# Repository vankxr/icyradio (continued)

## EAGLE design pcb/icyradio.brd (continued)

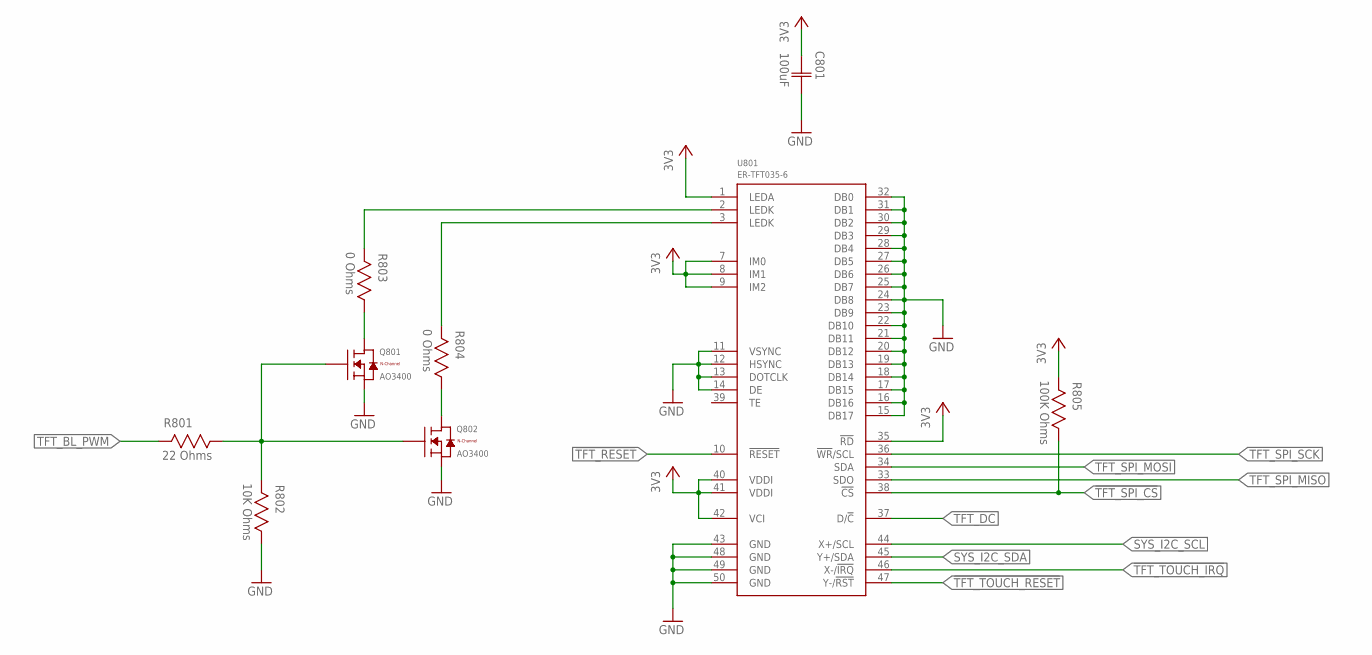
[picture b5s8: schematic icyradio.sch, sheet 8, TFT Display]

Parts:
C801: 100uF; CAP1206
Q801, Q802: AO3400; SOT23
R801: 22 Ohms; RES0603
R802: 10K Ohms; RES0603
R803, R804: 0 Ohms; RES0603
R805: 100K Ohms; RES0603
U801: ER-TFT035-6; FPC-50P

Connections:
3V3: C801.1 (C1), R805.2, U801.1 (LEDA), U801.7 (IM0), U801.8 (IM1), U801.9 (IM2), U801.35 (!RD), U801.40 (VDDI), U801.41 (VDDI), U801.42 (VCI); also elsewhere on the board
!TFT_RESET: U801.10 (!RESET); also elsewhere on the board
!TFT_SPI_CS: R805.1, U801.38 (!CS); also elsewhere on the board
!TFT_TOUCH_IRQ: U801.46 (X-/!IRQ!); also elsewhere on the board
!TFT_TOUCH_RESET: U801.47 (Y-/!RST!); also elsewhere on the board
GND: C801.2 (C2), Q801.2 (S), Q802.2 (S), R802.1, U801.11 (VSYNC), U801.12 (HSYNC), U801.13 (DOTCLK), U801.14 (DE), U801.15 (DB17), U801.16 (DB16), U801.17 (DB15), U801.18 (DB14), U801.19 (DB13), U801.20 (DB12), U801.21 (DB11), U801.22 (DB10), U801.23 (DB9), U801.24 (DB8), U801.25 (DB7), U801.26 (DB6), U801.27 (DB5), U801.28 (DB4), U801.29 (DB3), U801.30 (DB2), U801.31 (DB1), U801.32 (DB0), U801.43 (GND), U801.48 (GND), U801.49 (GND), U801.50 (GND); also elsewhere on the board
unnamed: Q802.3 (D), R804.1
unnamed: Q801.3 (D), R803.1
unnamed: Q801.1 (G), Q802.1 (G), R801.1, R802.2
SYS_I2C_SCL: U801.44 (X+/SCL); also elsewhere on the board
SYS_I2C_SDA: U801.45 (Y+/SDA); also elsewhere on the board
TFT_BL_K1: R803.2, U801.2 (LEDK)
TFT_BL_K2: R804.2, U801.3 (LEDK)
TFT_BL_PWM: R801.2; also elsewhere on the board
TFT_DC: U801.37 (D/!C!); also elsewhere on the board
TFT_SPI_MISO: U801.33 (SDO); also elsewhere on the board
TFT_SPI_MOSI: U801.34 (SDA); also elsewhere on the board
TFT_SPI_SCK: U801.36 (!WR!/SCL); also elsewhere on the board

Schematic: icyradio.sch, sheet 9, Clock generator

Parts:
C901, C902, C904, C905, C907: 100nF; CAP0603
C903, C906: DNP; CAP0603
R901, R902, R903: 100K Ohms; RES0603
R904, R905, R906, R907, R908, R909: 0 Ohms; RES0603
U901: DSC1201DE3-50M00000; VDFN6
U902: SI5351C; QFN20
X901: DNP; 4-SMD-3225

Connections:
3V3: C901.1 (C1), C902.1 (C1), C904.1 (C1), C905.1 (C1), C907.1 (C1), R902.2, R903.2, U901.6 (VDD), U902.10 (VDDOB), U902.11 (VDDOA), U902.14 (VDDOD), U902.18 (VDDOC), U902.20 (VDD); also elsewhere on the board
!CLK_MNGR_IRQ: R903.1, U902.3 (INTR); also elsewhere on the board
!CLK_MNGR_OE: R902.1, U902.7 (!OE); also elsewhere on the board
!CLK_MNGR_REFCLK_STDBY: R901.2, U901.1 (!STDBY); also elsewhere on the board
CLK_MNGR_CLK0: R904.2, U902.13 (CLK0)
CLK_MNGR_CLK1: R907.2, U902.12 (CLK1)
CLK_MNGR_CLK2: R905.2, U902.9 (CLK2)
CLK_MNGR_CLK3: R908.2, U902.8 (CLK3)
CLK_MNGR_CLK5: R909.2, U902.17 (CLK5)
CLK_MNGR_CLK6: R906.2, U902.16 (CLK6)
CLK_MNGR_REF: U901.4 (CLK), U902.6 (CLKIN)
CLK_MNGR_XTALA: C903.1 (C1), U902.1 (XA), X901.2 (1)
CLK_MNGR_XTALB: C906.1 (C1), U902.2 (XB), X901.4 (2)
DSP_MAIN_CLK: R906.1; also elsewhere on the board
FPGA_CLK1: R905.1; also elsewhere on the board
FPGA_CLK2: R907.1; also elsewhere on the board
FPGA_CLK3: R904.1; also elsewhere on the board
FPGA_CLK4: R908.1; also elsewhere on the board
GND: C901.2 (C2), C902.2 (C2), C903.2 (C2), C904.2 (C2), C905.2 (C2), C906.2 (C2), C907.2 (C2), R901.1, U901.3 (GND), U902.21 (GND), X901.1 (GND), X901.3 (GND); also elsewhere on the board
SMC_MAIN_CLK: R909.1; also elsewhere on the board
SYS_I2C_SCL: U902.4 (SCL); also elsewhere on the board
SYS_I2C_SDA: U902.5 (SDA); also elsewhere on the board

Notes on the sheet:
FPGA_CLK1 = 49.152 MHz (for 48 kHz audio sample rate) FPGA_CLK1 = 45.1584 MHz (for 44.1 kHz audio sample rate) FPGA_CLK2 = TBD MHz (general purpose clock) FPGA_CLK3 = TBD MHz (general purpose clock) FPGA_CLK4 = TBD MHz (general purpose clock) SMC_MAIN_CLK = 50 MHz (SMC main clock) DSP_MAIN_CLK = 20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

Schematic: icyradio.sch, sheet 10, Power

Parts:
C1001, C1002, C1006, C1010, C1011, C1015, C1017, C1020: 100nF; CAP0603
C1003, C1004, C1018, C1022, C1023, C1029, C1030: 4.7uF; CAP0603
C1005, C1008, C1012: 470pF; CAP0603
C1007, C1013, C1014, C1016: 100uF; CAP1206
C1009, C1019: 10nF; CAP0603
C1021, C1024, C1025, C1027, C1028: 1uF; CAP0603
C1026: 10uF; CAP0603
D1001: SP0503BAHT; SOT143
D1002, D1003: LED0603; 0603
F1001: PTC1206; 1206
L1001: 2.2uH; IND0805
L1002, L1004: 2.2uH; IND2520
L1003: 350nH; IND0805
L1005: 350nH; IND0603
R1001, R1002: 5.1K Ohms; RES0603
R1003: 274K Ohms; RES0603
R1004: 294K Ohms; RES0603
R1005, R1006, R1009, R1014, R1016: 100K Ohms; RES0603
R1007, R1010: 309K Ohms; RES0603
R1008: 64.9K Ohms; RES0603
R1011: 71.5K Ohms; RES0603
R1012: 510 Ohms; RES0603
R1013: 330 Ohms; RES0603
R1015: 820 Ohms; RES0603
U1001: MIC23155; DFN10
U1002: MIC23159; VQFN20
U1003: MIC2019; SOT23-6
U1004: ADP150UJZ-1.8; SOT23-5
U1005: ADP150UJZ-3.3; SOT23-5
U1006, U1007: MIC94305; DFN6
USB1001: USB-C-16P-SMD-FLAT-SIDE-TYPE-2

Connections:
1V2: C1006.1 (C1), C1007.1 (C1), L1001.1, R1003.2, U1002.17 (SNS); also elsewhere on the board
1V2_FB: R1003.1, R1004.2, U1002.16 (FB)
1V2_PGOOD: R1005.1, U1002.15 (PG); also elsewhere on the board
1V2_SOFTSTART: C1008.1 (C1), U1002.14 (SS)
1V8_CODEC_CLEAN: C1027.1 (C1), U1004.5 (OUT); also elsewhere on the board
3V3: C1015.1 (C1), C1016.1 (C1), C1024.1 (C1), L1004.2, R1005.2, R1006.2, R1009.2, R1010.2, R1013.2, R1016.2, U1002.10 (SNS), U1004.1 (VIN), U1004.3 (EN); also elsewhere on the board
3V3_ANA_RX_CLEAN: C1030.1 (C1), U1007.1 (VOUT), U1007.2 (VOUT); also elsewhere on the board
3V3_ANA_TXPLL_CLEAN: C1028.1 (C1), U1005.5 (OUT); also elsewhere on the board
3V3_ANA_TX_CLEAN: C1029.1 (C1), U1006.1 (VOUT), U1006.2 (VOUT); also elsewhere on the board
3V3_FB: R1010.1, R1011.2, U1002.11 (FB)
3V3_PGOOD: R1009.1, U1002.12 (PG); also elsewhere on the board
3V3_SOFTSTART: C1012.1 (C1), U1002.13 (SS)
3V6_ANA: C1010.1 (C1), C1013.1 (C1), C1022.1 (C1), C1023.1 (C1), C1025.1 (C1), L1002.2, R1007.2, U1001.3 (SNS), U1005.1 (VIN), U1005.3 (EN), U1006.4 (EN), U1006.5 (VIN), U1006.6 (VIN), U1007.4 (EN), U1007.5 (VIN), U1007.6 (VIN)
3V6_ANA_FB: R1007.1, R1008.2, U1001.4 (FB)
3V6_ANA_PGOOD: R1006.1, U1001.5 (PG); also elsewhere on the board
3V6_ANA_SOFTSTART: C1005.1 (C1), U1001.6 (SS)
5V0: C1001.1 (C1), C1002.1 (C1), C1003.1 (C1), C1004.1 (C1), C1011.1 (C1), C1014.1 (C1), C1017.1 (C1), C1018.1 (C1), C1019.1 (C1), L1003.2, L1005.1, R1012.2, U1001.2 (EN), U1001.8 (VIN), U1001.9 (VIN), U1002.1 (VIN), U1002.6 (VIN), U1002.7 (AVIN), U1002.9 (EN), U1002.18 (EN), U1002.20 (AVIN)
5V0_ANA_TXMIXER_CLEAN: C1020.1 (C1), C1021.1 (C1), L1005.2, U1003.1 (VIN); also elsewhere on the board
5V0_ANA_TXPA_CLEAN: C1026.1 (C1), U1003.6 (VOUT); also elsewhere on the board
!TXPA_OC: R1016.1, U1003.4 (!FAULT); also elsewhere on the board
DSP_D+: D1001.4, USB1001.A6 (D+), USB1001.B6 (D+); also elsewhere on the board
DSP_D-: D1001.3, USB1001.A7 (D-), USB1001.B7 (D-); also elsewhere on the board
GND: C1001.2 (C2), C1002.2 (C2), C1003.2 (C2), C1004.2 (C2), C1005.2 (C2), C1006.2 (C2), C1007.2 (C2), C1008.2 (C2), C1009.2 (C2), C1010.2 (C2), C1011.2 (C2), C1012.2 (C2), C1013.2 (C2), C1014.2 (C2), C1015.2 (C2), C1016.2 (C2), C1017.2 (C2), C1018.2 (C2), C1019.2 (C2), C1020.2 (C2), C1021.2 (C2), C1022.2 (C2), C1023.2 (C2), C1024.2 (C2), C1025.2 (C2), C1026.2 (C2), C1027.2 (C2), C1028.2 (C2), C1029.2 (C2), C1030.2 (C2), D1001.1, D1002.1 (C), D1003.1 (C), R1001.1, R1002.1, R1004.1, R1008.1, R1011.1, R1014.1, R1015.1, U1001.7 (AGND), U1001.10 (PGND), U1001.11 (PGND), U1002.2 (PGND), U1002.5 (PGND), U1002.8 (AGND), U1002.19 (AGND), U1002.21 (PGND), U1003.2 (GND), U1004.2 (GND), U1005.2 (GND), U1006.3 (GND), U1006.7 (GND), U1007.3 (GND), U1007.7 (GND), USB1001.A1/B12 (GND), USB1001.B1/A12 (GND); also elsewhere on the board
unnamed: L1004.1, U1002.4 (SW)
unnamed: L1001.2, U1002.3 (SW)
unnamed: R1001.2, USB1001.B5 (CC2)
unnamed: R1002.2, USB1001.A5 (CC1)
unnamed: F1001.2, USB1001.A4/B9 (VBUS), USB1001.B4/A9 (VBUS)
unnamed: L1002.1, U1001.1 (SW)
unnamed: C1009.1 (C1), D1001.2, F1001.1, L1003.1
unnamed: R1015.2, U1003.5 (ILIMIT)
unnamed: D1003.2 (A), R1013.1
unnamed: D1002.2 (A), R1012.1
TXPA_BIAS_EN: R1014.2, U1003.3 (EN); also elsewhere on the board

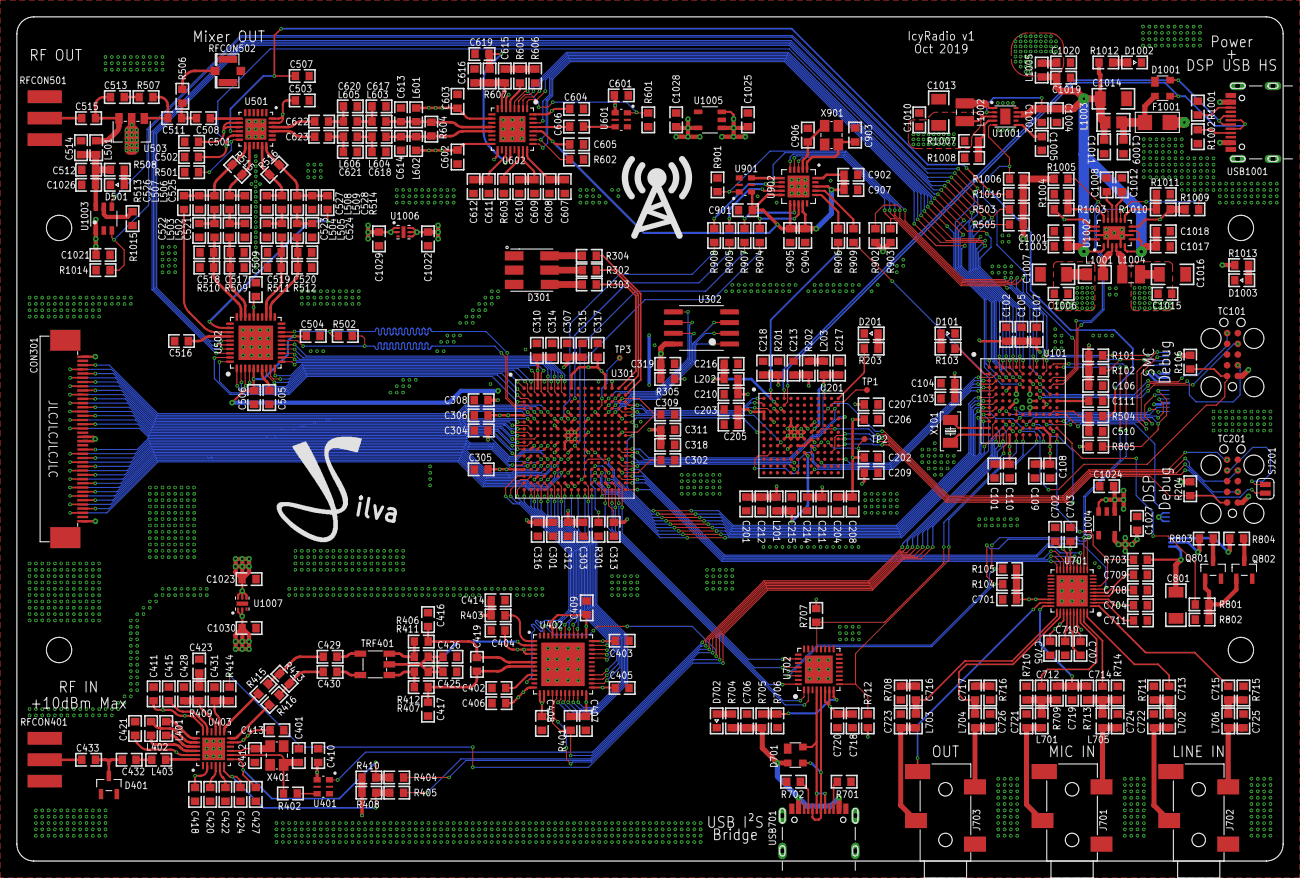
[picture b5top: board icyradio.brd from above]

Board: 4 copper layers, 150.0 x 100.0 mm, 386 parts (1 on the bottom side), 340 nets.

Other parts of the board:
U$1: JS_10MM
U$2: RADIO_10MM

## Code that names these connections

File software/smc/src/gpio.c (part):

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    // Port A
    GPIO->P[0].CTRL   = GPIO_P_CTRL_DRIVESTRENGTHALT_STRONG | (5 << _GPIO_P_CTRL_SLEWRATEALT_SHIFT)
                      | GPIO_P_CTRL_DRIVESTRENGTH_STRONG | (5 << _GPIO_P_CTRL_SLEWRATE_SHIFT);
    GPIO->P[0].MODEL  = GPIO_P_MODEL_MODE0_PUSHPULL                 // DSP_SPI_MOSI - USART3 - Location 0
                      | GPIO_P_MODEL_MODE1_INPUTPULL                // DSP_SPI_MISO - USART3 - Location 0
                      | GPIO_P_MODEL_MODE2_PUSHPULL                 // DSP_SPI_SCK - USART3 - Location 0
                      | GPIO_P_MODEL_MODE3_PUSHPULL                 // DSP_SPI_CS - USART3 - Location 0
                      | GPIO_P_MODEL_MODE4_DISABLED                 // NR
                      | GPIO_P_MODEL_MODE5_PUSHPULL                 // FPGA_SRESET
                      | GPIO_P_MODEL_MODE6_DISABLED                 // NR
                      | GPIO_P_MODEL_MODE7_PUSHPULL;                // TFT_SPI_MOSI - USART2 - Location 2
    GPIO->P[0].MODEH  = GPIO_P_MODEH_MODE8_INPUTPULL                // TFT_SPI_MISO - USART2 - Location 2
                      | GPIO_P_MODEH_MODE9_PUSHPULL                 // TFT_SPI_SCK - USART2 - Location 2
                      | GPIO_P_MODEH_MODE10_PUSHPULL                // TFT_SPI_CS - USART2 - Location 2
                      | GPIO_P_MODEH_MODE11_DISABLED                // NR
                      | GPIO_P_MODEH_MODE12_PUSHPULL                // RXADC_SHDN
                      | GPIO_P_MODEH_MODE13_PUSHPULL                // RXADC_DITH
                      | GPIO_P_MODEH_MODE14_PUSHPULL                // RXADC_GAIN
                      | GPIO_P_MODEH_MODE15_PUSHPULL;               // SMC_LED - TIM3 Channel 2 - Location 0
    GPIO->P[0].DOUT   = BIT(3) | BIT(5) | BIT(10) | BIT(12);
    GPIO->P[0].OVTDIS = 0;

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    GPIO->P[1].CTRL   = GPIO_P_CTRL_DRIVESTRENGTHALT_STRONG | (5 << _GPIO_P_CTRL_SLEWRATEALT_SHIFT)
                      | GPIO_P_CTRL_DRIVESTRENGTH_STRONG | (5 << _GPIO_P_CTRL_SLEWRATE_SHIFT);
    GPIO->P[1].MODEL  = GPIO_P_MODEL_MODE0_DISABLED                 // NR
                      | GPIO_P_MODEL_MODE1_INPUTPULLFILTER          // FPGA_CDONE
                      | GPIO_P_MODEL_MODE2_INPUTPULLFILTER          // FPGA_SMC_IRQ
                      | GPIO_P_MODEL_MODE3_DISABLED                 // NR
                      | GPIO_P_MODEL_MODE4_DISABLED                 // NR
                      | GPIO_P_MODEL_MODE5_INPUTPULLFILTER          // FPGA_CBSEL1
                      | GPIO_P_MODEL_MODE6_PUSHPULL                 // FPGA_CRESET
                      | GPIO_P_MODEL_MODE7_DISABLED;                // SMC_LFXTAL_P
    GPIO->P[1].MODEH  = GPIO_P_MODEH_MODE8_DISABLED                 // SMC_LFXTAL_N
                      | GPIO_P_MODEH_MODE9_DISABLED                 // NR
                      | GPIO_P_MODEH_MODE10_WIREDANDPULLUPFILTER    // DSP_RESET
                      | GPIO_P_MODEH_MODE11_DISABLED                // RXTUNER_IF_VAGC
                      | GPIO_P_MODEH_MODE12_PUSHPULL                // I2S_BRG_CFG
                      | GPIO_P_MODEH_MODE13_PUSHPULL                // I2S_BRG_RST
                      | GPIO_P_MODEH_MODE14_DISABLED                // SMC_MAIN_CLK
                      | GPIO_P_MODEH_MODE15_DISABLED;               // NR
    GPIO->P[1].DOUT   = BIT(1) | BIT(2) | BIT(5) | BIT(12);
    GPIO->P[1].OVTDIS = BIT(11);
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    // Port C
    GPIO->P[2].CTRL   = GPIO_P_CTRL_DRIVESTRENGTHALT_STRONG | (5 << _GPIO_P_CTRL_SLEWRATEALT_SHIFT)
                      | GPIO_P_CTRL_DRIVESTRENGTH_STRONG | (5 << _GPIO_P_CTRL_SLEWRATE_SHIFT);
    GPIO->P[2].MODEL  = GPIO_P_MODEL_MODE0_PUSHPULL                 // FPGA_SPI_CS - USART1 - Location 4
                      | GPIO_P_MODEL_MODE1_PUSHPULL                 // FPGA_SPI_SDI - USART1 - Location 4
                      | GPIO_P_MODEL_MODE2_INPUTPULL                // FPGA_SPI_SDO - USART1 - Location 4
                      | GPIO_P_MODEL_MODE3_PUSHPULL                 // FPGA_SPI_SCK - USART1 - Location 4
                      | GPIO_P_MODEL_MODE4_WIREDANDPULLUPFILTER     // RXTUNER_I2C_SDA - I2C1 - Location 0
                      | GPIO_P_MODEL_MODE5_WIREDANDPULLUPFILTER     // RXTUNER_I2C_SCL - I2C1 - Location 0
                      | GPIO_P_MODEL_MODE6_DISABLED                 // NR
                      | GPIO_P_MODEL_MODE7_DISABLED;                // NR
    GPIO->P[2].MODEH  = GPIO_P_MODEH_MODE8_INPUTPULLFILTER          // 3V3_PGOOD
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    // Port D
    GPIO->P[3].CTRL   = GPIO_P_CTRL_DRIVESTRENGTHALT_STRONG | (5 << _GPIO_P_CTRL_SLEWRATEALT_SHIFT)
                      | GPIO_P_CTRL_DRIVESTRENGTH_STRONG | (5 << _GPIO_P_CTRL_SLEWRATE_SHIFT);
    GPIO->P[3].MODEL  = GPIO_P_MODEL_MODE0_PUSHPULL                 // CODEC_RST
                      | GPIO_P_MODEL_MODE1_PUSHPULL                 // TFT_BL_PWM - TIM0 Channel 0 - Location 2
                      | GPIO_P_MODEL_MODE2_INPUTPULLFILTER          // TFT_TOUCH_IRQ
                      | GPIO_P_MODEL_MODE3_PUSHPULL                 // TFT_TOUCH_RESET
                      | GPIO_P_MODEL_MODE4_PUSHPULL                 // TFT_DC
                      | GPIO_P_MODEL_MODE5_DISABLED                 // NR
                      | GPIO_P_MODEL_MODE6_DISABLED                 // TXMIXER_TEMP
                      | GPIO_P_MODEL_MODE7_PUSHPULL;                // TFT_RESET
    GPIO->P[3].MODEH  = GPIO_P_MODEH_MODE8_DISABLED                 // NR
                      | GPIO_P_MODEH_MODE9_PUSHPULL                 // TXPLL_SDATA - USART4 - Location 1
                      | GPIO_P_MODEH_MODE10_DISABLED                // TXPLL_MUXOUT
                      | GPIO_P_MODEH_MODE11_PUSHPULL                // TXPLL_SCLK - USART4 - Location 1
                      | GPIO_P_MODEH_MODE12_PUSHPULL                // TXPLL_LE - USART4 - Location 1
                      | GPIO_P_MODEH_MODE13_PUSHPULL                // TXDAC_SCLK - USART5 - Location 1
                      | GPIO_P_MODEH_MODE14_DISABLED                // NR
                      | GPIO_P_MODEH_MODE15_DISABLED;               // RXTUNER_REFCLK_SEL - NU
    GPIO->P[3].DOUT   = BIT(2) | BIT(12);
    GPIO->P[3].OVTDIS = BIT(6) | BIT(10);

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                      | GPIO_P_MODEL_MODE1_DISABLED                 // NR
                      | GPIO_P_MODEL_MODE2_DISABLED                 // NR
                      | GPIO_P_MODEL_MODE3_DISABLED                 // NR
                      | GPIO_P_MODEL_MODE4_WIREDANDPULLUPFILTER     // SYS_I2C_SDA - I2C0 - Location 7
                      | GPIO_P_MODEL_MODE5_WIREDANDPULLUPFILTER     // SYS_I2C_SCL - I2C0 - Location 7
                      | GPIO_P_MODEL_MODE6_INPUTPULLFILTER          // CLK_MNGR_IRQ
                      | GPIO_P_MODEL_MODE7_DISABLED;                // NR
    GPIO->P[4].MODEH  = GPIO_P_MODEH_MODE8_PUSHPULL                 // TXDAC_SDIO - USART5 - Location 0
                      | GPIO_P_MODEH_MODE9_PUSHPULL                 // TXDAC_CS
                      | GPIO_P_MODEH_MODE10_PUSHPULL                // TXPA_BIAS_EN
                      | GPIO_P_MODEH_MODE11_INPUTPULLFILTER         // TXPA_OC
                      | GPIO_P_MODEH_MODE12_PUSHPULL                // TXDAC_RESET
                      | GPIO_P_MODEH_MODE13_INPUTPULLFILTER         // DSP_IRQ
                      | GPIO_P_MODEH_MODE14_DISABLED                // NR
                      | GPIO_P_MODEH_MODE15_PUSHPULL;               // TXMIXER_EN
    GPIO->P[4].DOUT   = BIT(6) | BIT(9) | BIT(11) | BIT(12) | BIT(13);
    GPIO->P[4].OVTDIS = 0;

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                      | GPIO_P_MODEL_MODE3_DISABLED                 // NC
                      | GPIO_P_MODEL_MODE4_DISABLED                 // NC
                      | GPIO_P_MODEL_MODE5_DISABLED                 // NR
                      | GPIO_P_MODEL_MODE6_PUSHPULL                 // CLK_MNGR_REFCLK_STDBY
                      | GPIO_P_MODEL_MODE7_PUSHPULL;                // TXPLL_EN
    GPIO->P[5].MODEH  = GPIO_P_MODEH_MODE8_PUSHPULL                 // TXPLL_MUTE
                      | GPIO_P_MODEH_MODE9_INPUTPULLFILTER          // TXPLL_LOCK
                      | GPIO_P_MODEH_MODE10_WIREDANDPULLUPFILTER    // AUDIO_I2C_SDA - I2C2 - Location 2
                      | GPIO_P_MODEH_MODE11_WIREDANDPULLUPFILTER    // AUDIO_I2C_SCL - I2C2 - Location 2
                      | GPIO_P_MODEH_MODE12_PUSHPULL                // CLK_MNGR_OE
                      | GPIO_P_MODEH_MODE13_DISABLED                // NC
                      | GPIO_P_MODEH_MODE14_DISABLED                // NC
                      | GPIO_P_MODEH_MODE15_DISABLED;               // NC
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
    // Debugger Route
    GPIO->ROUTEPEN &= ~(GPIO_ROUTEPEN_TDIPEN | GPIO_ROUTEPEN_TDOPEN);   // Disable JTAG
    GPIO->ROUTEPEN |= GPIO_ROUTEPEN_SWVPEN;                             // Enable SWO
    GPIO->ROUTELOC0 = GPIO_ROUTELOC0_SWVLOC_LOC0;                       // SWO on PF2

    // External interrupts
    GPIO->EXTIPSELL = GPIO_EXTIPSELL_EXTIPSEL0_PORTB            // FPGA_CDONE
                    | GPIO_EXTIPSELL_EXTIPSEL1_PORTB            // FPGA_SMC_IRQ
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
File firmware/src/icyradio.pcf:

set_io CLK1             C8      # IN    # Clock input 1
#set_io CLK2             K9      # IN    # Clock input 2
set_io CLK3             R9      # IN    # Clock input 3
set_io CLK4             F7      # IN    # Clock input 4
set_io RESETn           H16     # IN    # Global reset
set_io RED_LED          A16     # OUT   # RGB LED Red
set_io GREEN_LED        B16     # OUT   # RGB LED Green
set_io BLUE_LED         A15     # OUT   # RGB LED Blue
set_io QSPI_MEM_SCK     C14     # OUT   # QSPI Memory clock
set_io QSPI_MEM_CSn     E14     # OUT   # QSPI Memory chip select
set_io QSPI_MEM_IO0     C13     # IO    # QSPI Memory data input/output 0
set_io QSPI_MEM_IO1     E13     # IO    # QSPI Memory data input/output 1
set_io QSPI_MEM_IO2     D14     # IO    # QSPI Memory data input/output 2
set_io QSPI_MEM_IO3     D13     # IO    # QSPI Memory data input/output 3
set_io SMC_IRQn         K11     # OUT   # SMC Interrupt request output
set_io DSP_IRQn         F16     # OUT   # DSP Interrupt request output
set_io ADC_CLK          P1      # OUT   # ADC clock
set_io ADC_D0           T11     # IN    # ADC Data input 0
set_io ADC_D1           R10     # IN    # ADC Data input 1
set_io ADC_D2           T10     # IN    # ADC Data input 2
set_io ADC_D3           T9      # IN    # ADC Data input 3
set_io ADC_D4           T8      # IN    # ADC Data input 4
set_io ADC_D5           T7      # IN    # ADC Data input 5
set_io ADC_D6           R6      # IN    # ADC Data input 6
set_io ADC_D7           T6      # IN    # ADC Data input 7
set_io ADC_D8           R5      # IN    # ADC Data input 8
set_io ADC_D9           T5      # IN    # ADC Data input 9
set_io ADC_D10          R4      # IN    # ADC Data input 10
set_io ADC_D11          R3      # IN    # ADC Data input 11
set_io ADC_D12          T3      # IN    # ADC Data input 12
set_io ADC_D13          R2      # IN    # ADC Data input 13
set_io ADC_D14          T2      # IN    # ADC Data input 14
set_io ADC_D15          T1      # IN    # ADC Data input 15
set_io ADC_OF           R1      # IN    # ADC Overflow input
set_io ADC_OEn          P2      # OUT   # ADC Output enable output
set_io DAC_CLK          D2      # OUT   # DAC clock
set_io DAC_DCLK         D1      # OUT   # DAC Data clock
set_io DAC_D0           A7      # OUT   # DAC Data output 0
set_io DAC_D1           B7      # OUT   # DAC Data output 1
set_io DAC_D2           A6      # OUT   # DAC Data output 2
set_io DAC_D3           B6      # OUT   # DAC Data output 3
set_io DAC_D4           A5      # OUT   # DAC Data output 4
set_io DAC_D5           B5      # OUT   # DAC Data output 5
set_io DAC_D6           B4      # OUT   # DAC Data output 6
set_io DAC_D7           B3      # OUT   # DAC Data output 7
set_io DAC_D8           A2      # OUT   # DAC Data output 8
set_io DAC_D9           B2      # OUT   # DAC Data output 9
set_io DAC_D10          A1      # OUT   # DAC Data output 10
set_io DAC_D11          B1      # OUT   # DAC Data output 11
set_io DAC_D12          C2      # OUT   # DAC Data output 12
set_io DAC_D13          C1      # OUT   # DAC Data output 13
set_io SPI_SCK          R11     # IN    # Control SPI Slave SCK input
set_io SPI_MOSI         P11     # IN    # Control SPI Slave MOSI input
set_io SPI_MISO         P12     # OUT   # Control SPI Slave MISO output
set_io SPI_CSn          R12     # IN    # Control SPI Slave CS input
set_io BB_I2S_DSP_BCLK  E16     # OUT   # Baseband I2S DSP BCLK output
set_io BB_I2S_DSP_LRCLK D15     # OUT   # Baseband I2S DSP LRCLK output
set_io BB_I2S_DSP_SDOUT C16     # IN    # Baseband I2S DSP SDOUT input
set_io BB_I2S_DSP_SDIN  D16     # OUT   # Baseband I2S DSP SDIN output
set_io I2S_DSP_MCLK     K15     # IO    # Audio I2S DSP MCLK input/output
set_io I2S_DSP_BCLK     L16     # IO    # Audio I2S DSP BCLK input/output
set_io I2S_DSP_LRCLK    M15     # IO    # Audio I2S DSP LRCLK input/output
set_io I2S_DSP_SDOUT    K16     # IN    # Audio I2S DSP SDOUT input
set_io I2S_DSP_SDIN     M16     # OUT   # Audio I2S DSP SDIN output
set_io I2S_CODEC_MCLK   N16     # OUT   # Audio I2S CODEC MCLK output
set_io I2S_CODEC_BCLK   T16     # OUT   # Audio I2S CODEC BCLK output
set_io I2S_CODEC_LRCLK  R16     # OUT   # Audio I2S CODEC LRCLK output
set_io I2S_CODEC_SDOUT  P16     # IN    # Audio I2S CODEC SDOUT input
set_io I2S_CODEC_SDIN   P15     # OUT   # Audio I2S CODEC SDIN output
set_io I2S_BRG_MCLK     R15     # IN    # Audio I2S USB Bridge MCLK input
set_io I2S_BRG_BCLK     T13     # IN    # Audio I2S USB Bridge BCLK input
set_io I2S_BRG_LRCLK    T15     # IN    # Audio I2S USB Bridge LRCLK input
set_io I2S_BRG_SDOUT    R14     # IN    # Audio I2S USB Bridge SDOUT input
set_io I2S_BRG_SDIN     T14     # OUT   # Audio I2S USB Bridge SDIN output
#set_io EXP_IO0          E5      # XXX   # Expansion connector line 0
#set_io EXP_IO1          E4      # XXX   # Expansion connector line 1
#set_io EXP_IO2          E3      # XXX   # Expansion connector line 2
#set_io EXP_IO3          E2      # XXX   # Expansion connector line 3
#set_io EXP_IO4          F3      # XXX   # Expansion connector line 4
#set_io EXP_IO5          F2      # XXX   # Expansion connector line 5
#set_io EXP_IO6          F1      # XXX   # Expansion connector line 6
#set_io EXP_IO7          G2      # XXX   # Expansion connector line 7
#set_io EXP_IO8          G1      # XXX   # Expansion connector line 8
#set_io EXP_IO9          H2      # XXX   # Expansion connector line 9
#set_io EXP_IO10         H1      # XXX   # Expansion connector line 10
#set_io EXP_IO11         H3      # XXX   # Expansion connector line 11
#set_io EXP_IO12         J1      # XXX   # Expansion connector line 12
#set_io EXP_IO13         J2      # XXX   # Expansion connector line 13
#set_io EXP_IO14         K1      # XXX   # Expansion connector line 14
#set_io EXP_IO15         L1      # XXX   # Expansion connector line 15
#set_io EXP_IO16         K3      # XXX   # Expansion connector line 16
#set_io EXP_IO17         K4      # XXX   # Expansion connector line 17
#set_io EXP_IO18         L4      # XXX   # Expansion connector line 18
#set_io EXP_IO19         L3      # XXX   # Expansion connector line 19
#set_io EXP_IO20         M1      # XXX   # Expansion connector line 20
#set_io EXP_IO21         M2      # XXX   # Expansion connector line 21
#set_io EXP_IO22         M3      # XXX   # Expansion connector line 22
#set_io EXP_IO23         M4      # XXX   # Expansion connector line 23
#set_io EXP_IO24         M5      # XXX   # Expansion connector line 24
#set_io EXP_IO25         L5      # XXX   # Expansion connector line 25
#set_io EXP_IO26         M6      # XXX   # Expansion connector line 26
#set_io EXP_IO27         P4      # XXX   # Expansion connector line 27
#set_io EXP_IO28         P5      # XXX   # Expansion connector line 28
#set_io EXP_IO29         N6      # XXX   # Expansion connector line 29
#set_io EXP_IO30         L6      # XXX   # Expansion connector line 30
#set_io EXP_IO31         N7      # XXX   # Expansion connector line 31

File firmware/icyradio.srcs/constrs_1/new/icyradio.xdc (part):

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set_property PACKAGE_PIN L20 [get_ports {TRX_P0_TXDATA[11]}]
set_property PACKAGE_PIN L21 [get_ports {TRX_P0_TXDATA[10]}]
set_property PACKAGE_PIN K18 [get_ports TRX_FBCLK]
set_property PACKAGE_PIN J19 [get_ports TRX_DATA_CLK]
set_property PACKAGE_PIN K21 [get_ports TRX_TXFRAME]
set_property PACKAGE_PIN K22 [get_ports TRX_RXFRAME]
set_property PACKAGE_PIN J20 [get_ports TRX_CLK_OUT]
set_property PACKAGE_PIN J21 [get_ports {TRX_P1_RXDATA[11]}]
set_property PACKAGE_PIN J22 [get_ports {TRX_P1_RXDATA[10]}]
set_property PACKAGE_PIN K17 [get_ports {TRX_P1_RXDATA[9]}]
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set_property PACKAGE_PIN G22 [get_ports {TRX_CTRL_OUT[4]}]
set_property PACKAGE_PIN G21 [get_ports {TRX_P1_RXDATA[8]}]
set_property PACKAGE_PIN G13 [get_ports {TRX_SPI_ss_io[0]}]
set_property PACKAGE_PIN G15 [get_ports TRX_SPI_sck_io]
set_property PACKAGE_PIN G18 [get_ports TRX_SPI_io1_io]
set_property PACKAGE_PIN G17 [get_ports TRX_SPI_io0_io]
set_property PACKAGE_PIN G16 [get_ports {TRX_RESETn[0]}]
set_property PACKAGE_PIN F16 [get_ports TRX_EN]
set_property PACKAGE_PIN F15 [get_ports {TRX_EN_AGC[0]}]
set_property PACKAGE_PIN F14 [get_ports TRX_TXNRX]
set_property PACKAGE_PIN E21 [get_ports {TRX_CTRL_OUT[5]}]
set_property PACKAGE_PIN E19 [get_ports {TRX_CTRL_OUT[7]}]
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set_property PACKAGE_PIN D19 [get_ports {TRX_CTRL_OUT[6]}]
set_property PACKAGE_PIN D21 [get_ports {TRX_CTRL_OUT[2]}]
set_property PACKAGE_PIN D22 [get_ports {TRX_CTRL_OUT[1]}]
set_property PACKAGE_PIN F18 [get_ports {TRX_SYNC_IN[0]}]

set_property IOSTANDARD DIFF_SSTL135 [get_ports DDR3_CLK_IN_clk_p]

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set_property IOSTANDARD LVCMOS33 [get_ports {CODEC_I2S_sdata_in[0]}]
set_property IOSTANDARD LVCMOS33 [get_ports {CODEC_I2S_sdata_out[0]}]

set_property PACKAGE_PIN AA14 [get_ports AUDIO_I2C_scl_io]
set_property PACKAGE_PIN AA13 [get_ports AUDIO_I2C_sda_io]
set_property IOSTANDARD LVCMOS33 [get_ports AUDIO_I2C_sda_io]
set_property IOSTANDARD LVCMOS33 [get_ports I2S_BCLK_IN]
set_property IOSTANDARD LVCMOS33 [get_ports AUDIO_I2C_scl_io]
set_property PACKAGE_PIN W16 [get_ports {CODEC_I2S_sdata_out[0]}]
set_property PACKAGE_PIN AA15 [get_ports {CODEC_I2S_sdata_in[0]}]
set_property PACKAGE_PIN W17 [get_ports {CODEC_I2S_lrclk[0]}]
set_property PACKAGE_PIN V17 [get_ports {CODEC_I2S_bclk[0]}]
set_property IOSTANDARD LVCMOS33 [get_ports {SYNTH_SPI_ss_io[0]}]
set_property IOSTANDARD LVCMOS33 [get_ports SYNTH_SPI_io0_io]
set_property IOSTANDARD LVCMOS33 [get_ports SYNTH_SPI_io1_io]
set_property IOSTANDARD LVCMOS33 [get_ports SYNTH_SPI_sck_io]
set_property PACKAGE_PIN AA19 [get_ports SYNTH_SPI_sck_io]
set_property PACKAGE_PIN AB18 [get_ports SYNTH_SPI_io1_io]
set_property PACKAGE_PIN AA20 [get_ports {SYNTH_SPI_ss_io[0]}]
set_property PACKAGE_PIN AB17 [get_ports SYNTH_SPI_io0_io]
set_property IOSTANDARD LVCMOS33 [get_ports SYS_I2C_scl_io]
set_property IOSTANDARD LVCMOS33 [get_ports SYS_I2C_sda_io]
set_property PACKAGE_PIN Y22 [get_ports SYS_I2C_scl_io]
set_property PACKAGE_PIN AB22 [get_ports SYS_I2C_sda_io]
set_property IOSTANDARD LVCMOS33 [get_ports {PM_I2C_EN[0]}]
set_property PACKAGE_PIN AA18 [get_ports {PM_I2C_EN[0]}]
set_property IOSTANDARD LVCMOS33 [get_ports {CODEC_RESETn[0]}]
set_property PACKAGE_PIN Y19 [get_ports {CODEC_RESETn[0]}]

set_property PACKAGE_PIN W11 [get_ports FPGA_CLK0]
set_property IOSTANDARD LVCMOS33 [get_ports FPGA_CLK0]

create_power_rail USB_VBUS
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
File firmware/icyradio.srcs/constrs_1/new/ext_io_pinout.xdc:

# Header 1 (Near DDR)
## EXT_IO_1_1
#set_property IOSTANDARD LVCMOS33 [get_ports EXT_IO_1_1]
#set_property PACKAGE_PIN AA9 [get_ports EXT_IO_1_1]
set_property IOSTANDARD LVCMOS33 [get_ports EXT_I2C_scl_io]
set_property PACKAGE_PIN AA9 [get_ports EXT_I2C_scl_io]
## EXT_IO_1_2
#set_property IOSTANDARD LVCMOS33 [get_ports EXT_IO_1_2]
#set_property PACKAGE_PIN AA11 [get_ports EXT_IO_1_2]
set_property IOSTANDARD LVCMOS33 [get_ports EXT_I2C_sda_io]
set_property PACKAGE_PIN AA11 [get_ports EXT_I2C_sda_io]
## EXT_IO_1_3
#set_property IOSTANDARD LVCMOS33 [get_ports EXT_IO_1_3]
#set_property PACKAGE_PIN AB10 [get_ports EXT_IO_1_3]
## EXT_IO_1_4
#set_property IOSTANDARD LVCMOS33 [get_ports EXT_IO_1_4]
#set_property PACKAGE_PIN AB11 [get_ports EXT_IO_1_4]
## EXT_IO_1_5
#set_property IOSTANDARD LVCMOS33 [get_ports EXT_IO_1_5]
#set_property PACKAGE_PIN AA10 [get_ports EXT_IO_1_5]
## EXT_IO_1_6 - GND

# Header 2 (Near RFIC)
## EXT_IO_2_1 - GND
## EXT_IO_2_2
#set_property IOSTANDARD LVCMOS25 [get_ports EXT_IO_2_2]
#set_property PACKAGE_PIN A16 [get_ports EXT_IO_2_2]
## EXT_IO_2_3 - Clock from clock manager
## EXT_IO_2_4
#set_property IOSTANDARD LVCMOS25 [get_ports EXT_IO_2_4]
#set_property PACKAGE_PIN A15 [get_ports EXT_IO_2_4]
## EXT_IO_2_5 - GND
## EXT_IO_2_6
#set_property IOSTANDARD LVCMOS25 [get_ports EXT_IO_2_6]
#set_property PACKAGE_PIN A14 [get_ports EXT_IO_2_6]

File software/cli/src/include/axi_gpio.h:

#ifndef __AXI_GPIO_H__
#define __AXI_GPIO_H__

#include <stdint.h>
#include <pthread.h>
#include "utils.h"

#define AXI_GPIO_NUM_INSTANCES 3

#define AXI_GPIO_REG_GPIO_DATA      0x00
#define AXI_GPIO_REG_GPIO_IN_MASK   0x04

#define AXI_GPIO_OUTPUT 0
#define AXI_GPIO_INPUT  1

extern void *pAXIGPIOBase[AXI_GPIO_NUM_INSTANCES];

void axi_gpio_set_direction(uint8_t ubInst, uint8_t ubGPIO, uint8_t ubDirection);
uint8_t axi_gpio_get_direction(uint8_t ubInst, uint8_t ubGPIO);
void axi_gpio_set_value(uint8_t ubInst, uint8_t ubGPIO, uint8_t ubValue);
uint8_t axi_gpio_get_value(uint8_t ubInst, uint8_t ubGPIO);

// Instance 0 - axi_gpio_0 - Transceiver control
#define AXI_GPIO_TRX_INST      0

#define AXI_GPIO0_TRX_CTRL_IN0_BIT                   0 // BIT  0: TRX_CTRL_IN[0] (Fixed output)
#define AXI_GPIO0_TRX_CTRL_IN1_BIT                   1 // BIT  1: TRX_CTRL_IN[1] (Fixed output)
#define AXI_GPIO0_TRX_CTRL_IN2_BIT                   2 // BIT  2: TRX_CTRL_IN[2] (Fixed output)
#define AXI_GPIO0_TRX_CTRL_IN3_BIT                   3 // BIT  3: TRX_CTRL_IN[3] (Fixed output)
#define AXI_GPIO0_TRX_EN_AGC_BIT                     4 // BIT  4: TRX_EN_AGC (Fixed output)
#define AXI_GPIO0_TRX_SYNC_IN_BIT                    5 // BIT  5: TRX_SYNC_IN (Fixed output)
#define AXI_GPIO0_UP_ENABLE_BIT                      6 // BIT  6: axi_ad9361 up_enable (Fixed output)
#define AXI_GPIO0_UP_TXNRX_BIT                       7 // BIT  7: axi_ad9361 up_txnrx (Fixed output)
#define AXI_GPIO0_TRX_CTRL_OUT0_BIT                  8 // BIT  8: TRX_CTRL_OUT[0] (Fixed input)
#define AXI_GPIO0_TRX_CTRL_OUT1_BIT                  9 // BIT  9: TRX_CTRL_OUT[1] (Fixed input)
#define AXI_GPIO0_TRX_CTRL_OUT2_BIT                 10 // BIT 10: TRX_CTRL_OUT[2] (Fixed input)
#define AXI_GPIO0_TRX_CTRL_OUT3_BIT                 11 // BIT 11: TRX_CTRL_OUT[3] (Fixed input)
#define AXI_GPIO0_TRX_CTRL_OUT4_BIT                 12 // BIT 12: TRX_CTRL_OUT[4] (Fixed input)
#define AXI_GPIO0_TRX_CTRL_OUT5_BIT                 13 // BIT 13: TRX_CTRL_OUT[5] (Fixed input)
#define AXI_GPIO0_TRX_CTRL_OUT6_BIT                 14 // BIT 14: TRX_CTRL_OUT[6] (Fixed input)
#define AXI_GPIO0_TRX_CTRL_OUT7_BIT                 15 // BIT 15: TRX_CTRL_OUT[7] (Fixed input)
#define AXI_GPIO0_5V0_TRX_BIAS_T1_OCn_BIT           16 // BIT 16: 5V0_TRX_BIAS_T1_OCn (Fixed input)
#define AXI_GPIO0_5V0_TRX_BIAS_T2_OCn_BIT           17 // BIT 17: 5V0_TRX_BIAS_T2_OCn (Fixed input)
#define AXI_GPIO0_5V0_TRX_PA1_OCn_BIT               18 // BIT 18: 5V0_TRX_PA1_OCn (Fixed input)
#define AXI_GPIO0_5V0_TRX_PA2_OCn_BIT               19 // BIT 19: 5V0_TRX_PA2_OCn (Fixed input)
// BIT 20: RSVD
// BIT 21: RSVD
#define AXI_GPIO0_ADC_R1_MODE_BIT                   22 // BIT 22: axi_ad9361 adc_r1_mode (Fixed input)
#define AXI_GPIO0_DAC_R1_MODE_BIT                   23 // BIT 23: axi_ad9361 dac_r1_mode (Fixed input)
// BIT 24: RSVD
// BIT 25: RSVD
#define AXI_GPIO0_RST_AD9361_61M44_PERI_ARESETn_BIT 26 // BIT 26: rst_axi_ad9361_61M44 peripheral_aresetn (Fixed input)
// BIT 27: RSVD
// BIT 28: RSVD
// BIT 29: RSVD
// BIT 30: RSVD
#define AXI_GPIO0_TRX_RESETn_BIT                    31 // BIT 31: TRX_RESETn (Fixed output)

// Instance 1 - axi_gpio_1 - mmWave Synthesizer control
#define AXI_GPIO_SYNTH_INST    1

#define AXI_GPIO1_SYNTH_CE_BIT      0 // BIT  0: SYNTH_CE (Fixed output)
#define AXI_GPIO1_SYNTH_MUTE_BIT    1 // BIT  1: SYNTH_MUTE (Fixed output)
#define AXI_GPIO1_SYNTH_SYNC_BIT    2 // BIT  2: SYNTH_SYNC (Fixed output)
// BIT  3: RSVD
// BIT  4: RSVD
// BIT  5: RSVD
// BIT  6: RSVD
// BIT  7: RSVD
#define AXI_GPIO1_SYNTH_LD_BIT      8 // BIT  8: SYNTH_LD (Fixed input)
// BIT  9: RSVD
// BIT 10: RSVD
// BIT 11: RSVD
// BIT 12: RSVD
// BIT 13: RSVD
// BIT 14: RSVD
// BIT 15: RSVD
// BIT 16: RSVD
// BIT 17: RSVD
// BIT 18: RSVD
// BIT 19: RSVD
// BIT 20: RSVD
// BIT 21: RSVD
// BIT 22: RSVD
// BIT 23: RSVD
// BIT 24: RSVD
// BIT 25: RSVD
// BIT 26: RSVD
// BIT 27: RSVD
// BIT 28: RSVD
// BIT 29: RSVD
// BIT 30: RSVD
#define AXI_GPIO1_SYNTH_RESETn_BIT  31 // BIT 31: SYNTH_RESETn (Fixed output)

// Instance 2 - axi_gpio_2 - System control
#define AXI_GPIO_SYS_INST      2

#define AXI_GPIO2_CLK_WIZ0_LOCKED_BIT                    0 // BIT  0: clk_wiz_0 locked (Fixed input)
#define AXI_GPIO2_MIG_MMCM_LOCKED_BIT                    1 // BIT  1: mig_7series_0 mmcm_locked (Fixed input)
#define AXI_GPIO2_PCIE_MMCM_LOCKED_BIT                   2 // BIT  2: axi_pcie_0 mmcm_lock (Fixed input)
// BIT  3: RSVD
#define AXI_GPIO2_MIG_INIT_CALIB_COMPLETE_BIT            4 // BIT  4: mig_7series_0 init_calib_complete (Fixed input)
#define AXI_GPIO2_PCIE_USER_LINK_UP_BIT                  5 // BIT  5: axi_pcie_0 user_link_up (Fixed input)
#define AXI_GPIO2_RV32_TRAPPED_BIT                       6 // BIT  6: picorv32_0 trap (Fixed input)
// BIT  7: RSVD
#define AXI_GPIO2_CM4_WAKE_BIT                          8 // BIT 8: CM4_WAKE (Fixed output)
#define AXI_GPIO2_CODEC_RSTn_BIT                        9 // BIT 9: CODEC_RSTn (Fixed output)
#define AXI_GPIO2_PM_I2C_EN_BIT                        10 // BIT 10: PM_I2C_EN (Fixed output)
#define AXI_GPIO2_CLK_MNGR_OEn_BIT                     11 // BIT 11: CLK_MNGR_OEn (Fixed output)
// BIT 12: RSVD
// BIT 13: RSVD
// BIT 14: RSVD
// BIT 15: RSVD
#define AXI_GPIO2_RST_MIG_166M_PERI_ARESETn_BIT         16 // BIT 16: rst_mig_7series_0_166M peripheral_aresetn (Fixed input) - This is the reset for the DDR3 controller AXI interface only
#define AXI_GPIO2_RST_CLK_WIZ0_250M_PERI_ARESETn_BIT    17 // BIT 17: rst_clk_wiz_0_250M peripheral_aresetn (Fixed input) - This is the reset for the DDR3 controller, known as sys_rst_n in the Xilinx IP
#define AXI_GPIO2_RST_FPGA_CLK1_49M152_PERI_ARESETn_BIT 18 // BIT 18: rst_FPGA_CLK1_49M152 peripheral_aresetn (Fixed input) - This is the reset for the I2S module
// BIT 19: RSVD
// BIT 20: RSVD
// BIT 21: RSVD
// BIT 22: RSVD
// BIT 23: RSVD
#define AXI_GPIO2_RST_MIG_166M_AUX_RESET_IN_BIT         24 // BIT 24: rst_mig_7series_0_166M aux_reset_in (Fixed output) - Asserting this will reset the DDR3 controller AXI interface only
#define AXI_GPIO2_RST_CLK_WIZ0_250M_AUX_RESET_IN_BIT    25 // BIT 25: rst_clk_wiz_0_250M aux_reset_in (Fixed output) - Asserting this will reset the DDR3 controller, known as sys_rst_n in the Xilinx IP
#define AXI_GPIO2_RST_FPGA_CLK1_49M152_AUX_RESET_IN_BIT 26 // BIT 26: rst_FPGA_CLK1_49M152 aux_reset_in (Fixed output) - Asserting this will reset the I2S module
// BIT 27: RSVD
// BIT 28: RSVD
// BIT 29: RSVD
#define AXI_GPIO2_RV32_RESETN_BIT                       30 // BIT 30: picorv32_0 resetn (Fixed output) - Asserting this will reset the PicoRV32 CPU
#define AXI_GPIO2_SYS_AUX_RESET_BIT                     31 // BIT 31: sys_aux_reset (Fixed output) - Asserting this will reset the entire system, including the DDR3 controller since the 250 MHz DDR3 source clock MMCM is reset

#endif // __AXI_GPIO_H__

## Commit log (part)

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2020-05-11 Rename DDC to QDDC for consistency
2020-05-18 Tidy up HDL Add SSB modulation MATLAB script
2020-05-30 Move upconverter to other repository Small I2S master Verilog change Add dsp OpenOCD script
2020-05-30 Add dsp OpenOCD script
2020-07-03 Fix DSP generated baseband Add TX spectrum pictures
2020-07-06 Remove TX related stuff from master branch
2020-07-06 Remove unused fm_demod prototype
2020-07-06 Fix typo
2020-07-07 First SSB TX success
2020-07-07 Add missing AUXDAC top option
2020-07-09 Remoce DAC AC swing limiting resistors Change PLL reference AC couple capacitor to 10pF
2020-07-14 Added block diagram
2020-07-14 Added block diagram to README
2020-07-14 Fix IQ swap functionality on QDDC Remove unnecessary reset bit check
2020-07-14 Add a tuner to the QDUC Fix indentation in FPGA library Reduce NCO LUT size to 512x4 instead of 1024x4 Disable QSPI Verilog module
2020-07-14 Add QDUC configuration functions
2020-07-14 Mix audio channels in DSP Test TX with CP2615 bridge
2020-07-15 Add DSP oscillator
2020-07-15 Narower audio filter Implement oscillator
2020-07-15 Add SPI slave interface to DSP
2020-07-15 Move SPI registers to DTCM Move SPI ISR to ITCM
2020-07-15 Add SPI macros
2020-07-16 Fix PIO macros
2020-07-17 Fix oscillator and add FIR checks
2020-07-17 Revert some SPI stuff since it was too much
2020-07-17 Add Squelch
2020-07-21 Fix DSP cache macro Fix baseband I2S DMA init typo Moved all ISRs to ITCM memory Wait until XDMAC channel is disabled/enabled Fix error in xdmac_ch_get_remaining_xfers Re-add DSP SPI interface using 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
2020-07-21 Fix DSP cache macro Moved all ISRs to ITCM memory Wait until XDMAC channel is disabled/enabled Fix error in xdmac_ch_get_remaining_xfers Re-add DSP SPI interface using DMA
2020-07-25 Add errata section to the README
2020-08-03 Add missing parenthesis
2020-08-06 Fixed typo
2020-08-06 Added baseband decimation Removed files related to other branches Changed TXPLL reference frequency
2020-08-06 Update block diagram
2020-08-07 Tune TX DAC DC offset Add DSP TRNG library Tiny renames and fixes
2020-08-07 Remove DSP SPI completely
2020-08-07 Re-added DSP_UNRESET macro
2020-08-23 Rename mixer modules Added QSPI DP RAM Reworked QSPI module Decimate by 2 before QDDC tuner
2020-08-23 Added QSPI management routines
2020-08-23 Added more R820T2 register documentation
2020-08-23 Changed SSB modulation sumilation to generate sparse FIR header
2020-08-23 Add Backup RAM section to linker script and utility macros
2020-08-23 DSP running at 348 MHz (out of spec, but working) and changes to support that frequency
2020-08-23 Add new sparse Hilbert filter Separate RX and TX DSP chains
2020-08-23 Remove extra new line
2020-08-23 Remove mic DSP software
2020-08-24 Update block diagram with more details
2020-09-09 Change final amplifier to ADL5610
2020-09-09 Change DSP AGC parameters Change source to I2S bridge Change TX IF to 525 MHz instead of 425 MHz
2020-09-16 Fixed line width
2020-10-12 Forgot to add RLE library to stage
2020-10-12 Change TFT backlight PWM frequency to 50 kHz Remove RX Tuner frequency select and fix frequency to new 0.5ppm 32 MHz TCXO
2020-10-13 Change TX PLL loop filter
2020-10-25 Fix typo in CMU function
2020-10-25 Extend PMC library Change CPU frequency to 360 MHz (out of spec, confirmed working)
2020-10-29 Added MATRIX library
2020-10-29 Implement new PMC API
2020-10-29 Add udev rules
2020-10-30 First working USB code Finish implementing new PMC API
2020-10-30 Add SSB description to README
2020-10-30 Change LICENSE to GPLv3
2020-10-30 Add master description to README
2020-10-30 Update license in README
2020-10-30 Rephrasing license
2020-10-30 Change frequency and I2S mux config
2020-11-01 Invalidate caches after reading unique ID from flash (costed me about 5h of debugging, lol)
2020-11-01 Change small comment
2020-11-01 Add AFEC API to measure temperature (toasy IC)
2020-11-07 Changes to HDL
2020-11-08 Add register to CIC output stage and truncate result to output size Changed DDC and DUC parameters
2020-11-08 Re-tune R820T2 when coming back from sleep
2020-11-08 Add CLI application to dump samples to stdout
2020-11-21 Update libusb cli test apps
2020-11-21 Update SMC CMSIS
2020-11-28 Implement PLL IP in HDL to reduce input frequency Run ADC at half the frequency to remove first QDDC CIC decimation stage Print HDL related frequencies on SMC startup
2020-11-28 Change baseband rate to 768 ksps Align cached buffers to 32 byte-boundary to prevent undefined behaviour when invalidating unaligned cache
2020-11-28 Align cached buffers to 32 byte-boundary to prevent undefined behaviour when invalidating unaligned cache
2020-12-19 Change some comments on clocks
2020-12-19 Try to brute-force mixer temperature with unofficial information, seems to work better than before
2020-12-19 Update R820T2 register init descriptions with documentation
2020-12-31 Fix indentations
2021-01-23 Fix error in SI5351 fractional divider/multiplier formula
2021-01-23 Use SI5351 PLL name macros Write SI5351 MultiSynth registers in the correct order to produce accurate clock frequencies
2021-01-31 Update arm gcc toolchain
2021-01-31 Add cli correct IDE compiller config
2021-01-31 Dont config USHFRCO Dont disable AUXHFRCO
2021-02-05 Prevent compiller from optimizing startup RAM data copy
2021-02-22 Pipelined NCO and real-complex multiplier Saturator is now synchronous, which allows running design at higher frequencies
2021-02-22 DSP USB callbacks, vendor requests moved to main.c New attempt at SPI control interface, added DSP base code, working so far
2021-03-24 Updated block diagram
2021-03-30 Start hardware v2 schematic work
2021-05-13 Change TCXO
2021-06-08 Sync work
2021-06-10 Work on PCB
2021-06-10 Remove old documentation and utilities Add AD9361/3 transceivers documentation
2021-06-10 Fix images in README
2021-06-21 Restore lower level block diagram
2021-07-27 Major design changes
2021-09-23 PCB Work
2021-09-26 Remove iCE40 design files Add new Vivado project for new FPGA
2021-09-26 Add kernel driver development environment
2021-09-26 Work on schematic
2021-10-23 Update top level block diagram
2021-10-23 Removed old files from docs Added datasheets and important reference documents
2021-11-07 Vivado sync
2022-04-25 Added missing rle_encode tool
2022-04-25 Add liquid-dsp and libfec
2022-04-26 Add libopus
2022-04-30 Multithreaded PnR
2022-04-30 Update MATLAB filter simulator
2022-05-09 Add FreeRTOS
2022-05-09 Update HDL
2022-05-09 Update simulator
2022-05-12 Add core name print to DSP
2022-05-12 Update DSP launch.json to bring SWO back to life
2022-09-16 Changes for lab tests
2022-09-26 Work on Schematic and PCB
2022-09-26 Add Eagle schematic rename scripts to gitibnore
2022-09-30 Update Device and Core CMSIS Add script to generate GCC defines for VSCode configuration
2022-10-02 Update documents and add some missing ones Removed block diagram and made the top-level block diagram the default, as they were redundant
2022-10-02 Removed SMC and DSP software as they are no longer present in the v2 design
2022-10-22 Remove second DDR3 chip as it was impossible to route with a 6-layer board Update HDL project to reflect hardware changes
2022-10-28 DDR3 routing finished Some more PCB progress
2022-10-29 PCB routing
2022-11-11 First nothing to do!
2022-11-17 Some PCB touches
2022-11-17 Add schematic PDF and first PCB renders
2022-11-30 Add FUNDING.yml
2023-01-13 Silk screen done
2023-02-26 Minor changes
2023-02-26 Remove dedicated DDR3 oscillator
2023-02-26 Finish checklist and generate gerbers
2023-03-05 Some PCB rectifications and removal of old gerbers
2023-03-12 Set values for current limit switches Final touches for production Re-generate gerbers, schematic PDF and PCB pictures
2023-09-18 Add Power Management Controller MCU software Start working on MCU peripheral libraries for the ATSAMD
2023-09-19 Add LT7182S library Progress in PMC software for basic board bringup
2023-09-19 Mention LT7182S WP pin errata
2023-09-21 Kernel driver work for basic board testing
2023-09-21 PMC software work
2023-09-22 Add more errata and details
2023-09-22 Add expansion board template
2023-10-01 Optimize PMC build for size instead of O3 Add some utility functions to LT7182S library to reduce code size
2023-10-01 Basic kernel driver that implements mmap
2023-10-01 Add CLI app for system testing
2023-10-01 Update PCB pad color
2023-10-05 Tons of work on CLI testing app mmWave Synthesizer library partly added, untested AD9361 library refactored and rewritten
2023-10-05 Change comments in kernel driver file to reflect HDL changes
2023-10-06 Add expansion board PCB template
2023-10-11 Work on kernel driver Add more fops Implement IRQs Implement DMA buffer allocation and mamping to userspace
2023-10-11 Work on CLI software
2023-10-13 Add IOCTL to query number of IRQ lines allocated Misc driver changes
2023-10-13 Fix power tree in schematic
2023-10-13 Fix bug in LT7182S library - L11 write Misc PMC software changes
2023-10-15 Add IOCTL call to flush IRQs, allowing a blocked thread polling for interrupts to be unblocked Add udev rules Minor driver changes
2023-10-15 Add AXI DNA peripheral to read FPGA serial number Minor CLI software changes
2023-10-15 Fix board shutting down when CM4 reboots
2023-10-15 Add SoapySDR module with most of the libraries needed
2023-10-16 Add individual README files to each software subfolder Add RISC V firmware folder
2023-10-17 Add more documentation
2023-10-26 Fix mmWave Synth not locking Change AXI Quad SPI select to bool
2023-10-29 Unmute mmWave synth on lock
2023-10-31 Add SoapySDR module github workflow
2023-10-31 Add PMC software github workflow
2023-10-31 Test Soapy build on arm64
2023-10-31 Add CLI tool github workflow
2023-10-31 Remove leftover file from drawio Add gitignore to prevent future accidental commits of such files
2023-11-01 Build SoapySDR module debian package
2023-11-01 Move udev rules out
2023-11-01 Build CLI tool debian package
2023-11-01 Build kernel driver DKMS debian package
2023-11-01 Forgot to install dkms
2023-11-01 Rename soapy-module-icyradio to soapysdr-module-icyradio
2023-11-13 HDL: Add level/edge interrupt modes and polarity inversion HDL: Stop using IIC IP GPOs
2023-11-13 Driver: Ignore dependency files
2023-11-13 PMC: Reboot CM4 instead of shutting system off to work around crappy SD Cards that won't allow it to properly reboot
2023-11-13 Soapy: Change time interval in AXI DMAC checks Soapy: Add timeouts to AXI IIC transactions Soapy: Fix AXI IIC race conditions and add workaround for IP Core bugs Soapy: Disable AXI IIC GPOs Soapy: Al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
2023-11-19 Fix some typos in the README, etc
2023-11-19 Clarify some signals in the block diagram
2023-11-20 driver: Read the device DNA (serial) on probe driver: Add IOCTL call to retrieve the DNA for faster device enumeration and identification driver: Change initialization order when probing driver: Misc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
2023-11-20 exp_template: Change optimization to O3 instead of Os since we are not space constrained exp_template: Add integer versions of the ADC readout methods exp_template: Rework SERCOM library, adding supp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
2023-11-20 soapy: Use the new IOCTL call on enumeration soapy: Si5351: Move device ID/revision support checks to constructor instead of init function soapy: Si5351: Normalize phase to 0-360 instead of throwing 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
2024-02-19 hdl: New SPI/QSPI modules hdl: New GPIO modules hdl: Major changes
2024-02-19 soapy: mmWave Synth work soapy: Driver for new AXI GPIO module soapy: Driver for new AXI SPI module soapy: Fix typos in exception messages in AXI I2S soapy: Fix wrong clock divider calculation in AXI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
2024-02-19 exp: Add ROM-like memory for reading via I2C
2024-02-19 cli: Enable Si5351 fanout cli: Add new IOCTL
2024-02-21 driver: Fix build errors on kernel >6.3 driver: Bump RPi kernel branch to stable_20240124
2024-03-27 Port HDL project to vivado 2023.2 HDL work
2024-03-27 driver: Ensure compatibility with newer kernel versions driver: Add IRQ noflush ioctl driver: Read DNA data from the kernel driver: Add IRQ spinlock driver: Add device table mutex and per-device mutex
2024-03-27 Update soapy build flow
2024-03-27 driver: Use kernel built-in logging priorities
2026-03-26 hdl: Update I2S Core hdl: Misc cleanup hdl: Add timing constraints
